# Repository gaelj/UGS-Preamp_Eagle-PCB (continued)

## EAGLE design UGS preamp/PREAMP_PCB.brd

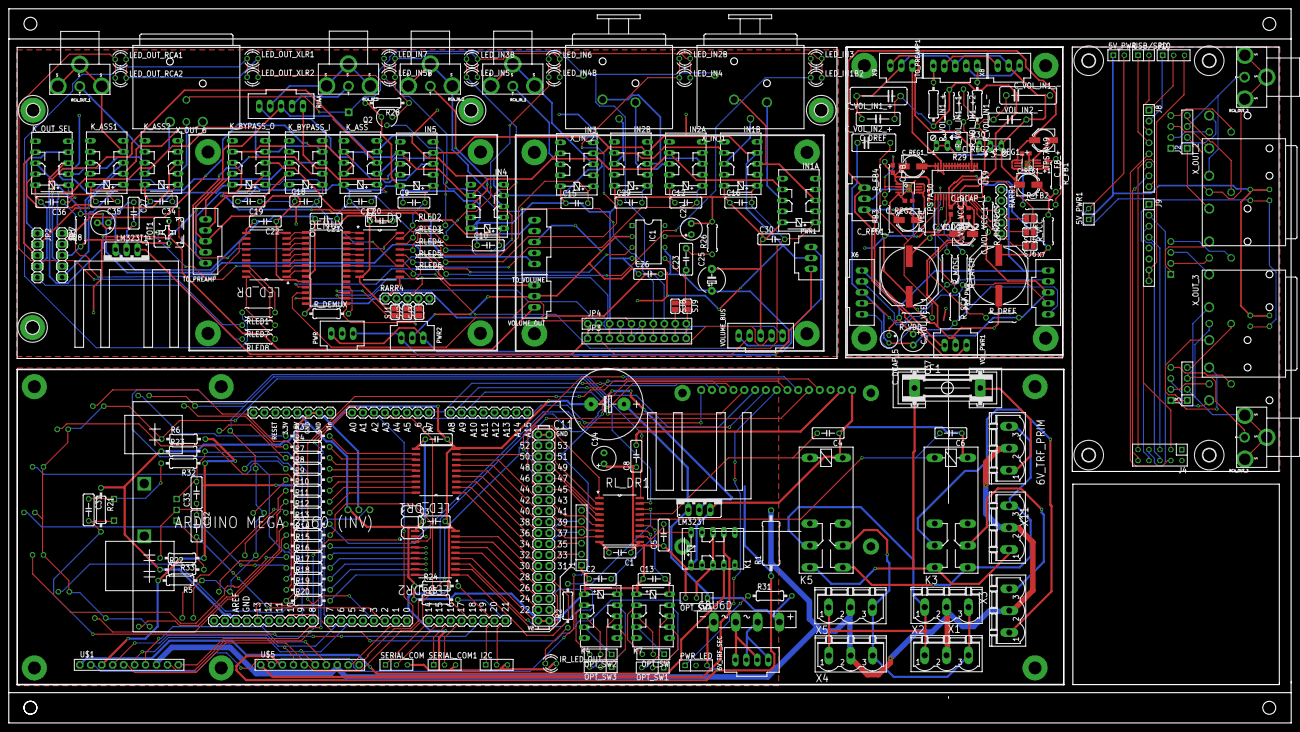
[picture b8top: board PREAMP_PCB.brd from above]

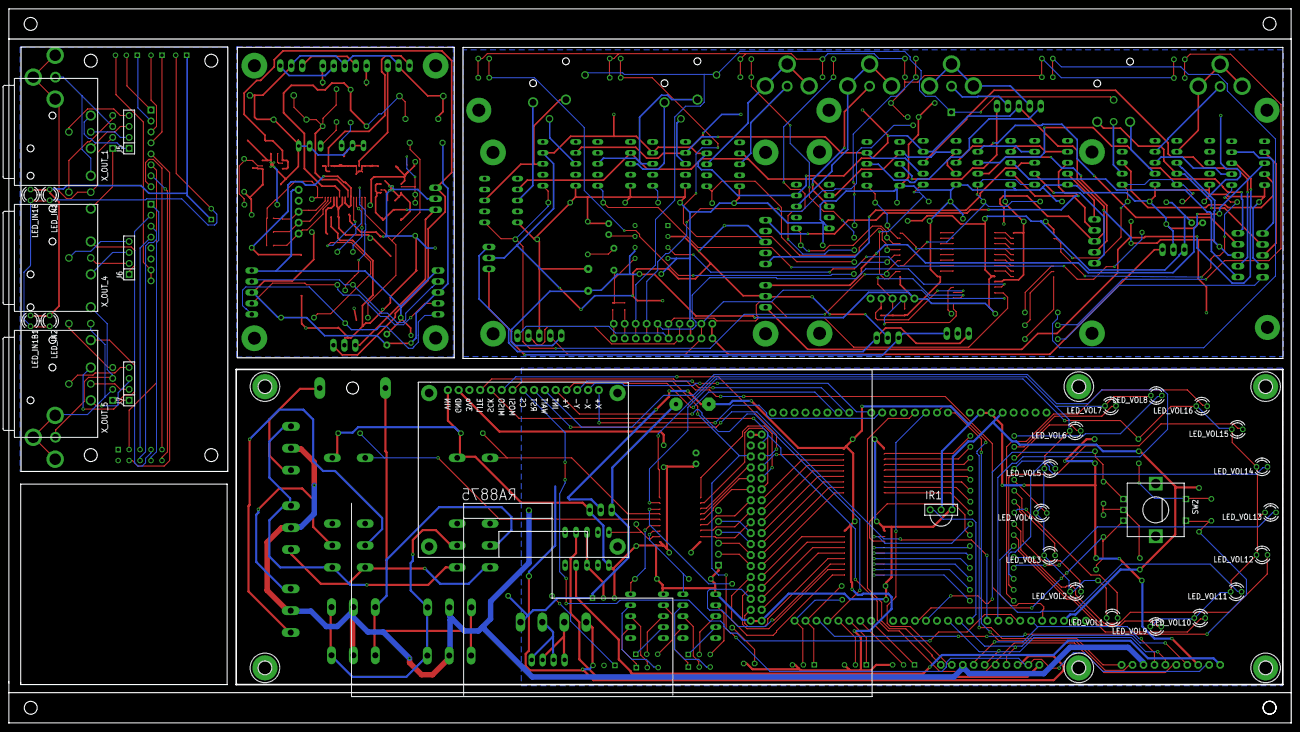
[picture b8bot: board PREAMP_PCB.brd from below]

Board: 2 copper layers, 297.4 x 165.6 mm, 284 parts (34 on the bottom side), 299 nets.

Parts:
5V_PWR, 5V_PWR1: 5V PWR; M1X2
6V_TRF_PRIM: 5V_TRF_PRIM; MSTBV3
6V_TRF_SEC: 6V_TRF_SEC; 70543-04
C1, C2, C3, C4, C5, C6, C7, C8, C9, C10, C12, C13, C15, C16, C17, C18, C19, C20, C21, C22, C26, C27, C29, C30, C31, C32, C33, C34, C35, C36: 100n; C050-025X075
C11: 4700µ; E7,5-16
C14, C28, C37: 470µ; E2,5-6
C23: 47nF; C5B3
C24: 1µF; E2,5-5
C25: 100µF; E5-6
C_DCAP_1: 100n; C0603
C_DCAP_2: 10µ24V; PANASONIC_C
C_DCAP_5: 1µ 5V; E1,8-4
C_DREF: 470n; C075-042X103
C_FB_+: 10n; C0603
C_FB_-: 10n; C0603
C_REG1_+, C_REG1_+1, C_REG1_-, C_REG1_-1: 10µ24V; PANASONIC_C
C_REG2_+, C_REG2_-: 10n; C0603
C_VOL_IN1_+, C_VOL_IN1_-: 1n; C102-043X133
C_VOL_IN2_+, C_VOL_IN2_-: 100p; C075-032X103
C_VOL_VCC_1: 470µ 24V; PANASONIC_H13
C_VOL_VCC_2: 100n; C0603
C_VOL_VEE_1: 470µ 24V; PANASONIC_H13
C_VOL_VEE_2: 100n; C0603
DEMUX: 23S17; SO28W
F1: 300mA; GSH15
GBU6D: 6A; GBU4S
H1, H3, H6, H7, H8, H9, H11, H12, H13, H15: MOUNT-PAD-ROUND3.0; 3,0-PAD
H2, H4, H5, H10: MOUNT-HOLE3.0; 3,0
I2C: CON_HEADER_1X03-PTH; M1X3
IC1: LM386; DIL08
IN1A: IN1A; G6H2-100
IN1B: IN1B; G6H2-100
IN2A: IN2A; G6H2-100
IN2B: IN2B; G6H2-100
IN3: IN3; G6H2-100
IN4: IN4; G6H2-100
IN5: IN5; G6H2-100
IR1: IR; TSOP17_TB1
IR_LED_OUT: IR out; LED3MM
J1: CON_HEADER_1X06-PTH; M1X6
J2, J3: CON_HEADER_1X04; M1X4
J4: DAC; M2X5
J5: CON_OUT_1; M1X4
J6: CON_OUT_2; M1X4
J7: CON_OUT_3; M1X4
J8: ARD1; M1X8
J9: ARD2; M1X8
J10: SERIAL; M1X3
JP1: OUT/IN SELECTED; 1X05
JP2: OUTPUT; 1X05
JP3, JP4: PINHD-1X10; 1X10-BIG
K1, K4, K7: G6H2-100
K3, K5: 4052; F4052
K_ASS: K_ASS_I; G6H2-100
K_ASS1: K_ASS_O_GND; G6H2-100
K_ASS2: K_ASS_O; G6H2-100
K_BYPASS_I: BYPASS_I; G6H2-100
K_BYPASS_O: BYPASS_O; G6H2-100
K_OUT_SEL: K_OUT_SEL; G6H2-100
LED_DR, LED_DR1, LED_DR2: 2803; SOIC127P1030X265-18N
LED_IN1, LED_IN1B, LED_IN1B1, LED_IN1B2, LED_IN2, LED_IN2B, LED_IN3, LED_IN3B, LED_IN4, LED_IN4B, LED_IN5, LED_IN5B, LED_IN6, LED_IN7: LED3MM
LED_OUT_RCA1, LED_OUT_RCA2: LED3MM
LED_OUT_XLR1, LED_OUT_XLR2: LED3MM
LED_VOL1, LED_VOL2, LED_VOL3, LED_VOL4, LED_VOL5, LED_VOL6, LED_VOL7, LED_VOL8, LED_VOL9, LED_VOL10, LED_VOL11, LED_VOL12, LED_VOL13, LED_VOL14, LED_VOL15, LED_VOL16: LED3MM
LM323T, LM323T1: 5V REG; TO220S
OPT_SW, OPT_SW1, OPT_SW2, OPT_SW3, OPT_SW4: CON_HEADER_1X03-PTH; M1X3
PCB2: ARDUINO_MEGA2560_INV
POT1: 500k; B25P
PRE_PWR: TO_PRE_PWR; 70543-03
PWR, PWR1, PWR2: PWR; 70543-03
PWR_LED: CON_HEADER_1X03-PTH; M1X3
Q2: BS170; SOT54E
R1: 10R 1W; 0411/15
R2, R32, R33: 330; 0207/10
R3, R4, R7, R8, R9, R10, R11, R12, R13, R14, R15, R16, R17, R18, R19, R20, R31: 1k; 0207/10
R5, R6, R21, R22, R23, R24, R25: 10k; 0207/10
R26: 10; 0207/7
R27: 500k; 0207/7
R28: 10k PWM; 0207/10
R29, R30: 20k; RJ9W
RARR1, RARR4: 10k; 1X05
RCA_IN_1: IN1; MONO_JACK
RCA_IN_2: IN2; MONO_JACK
RCA_IN_3: IN3_RIAA; MONO_JACK
RCA_OUT_1: OUT1; MONO_JACK
RCA_OUT_2: OUT_L; MONO_JACK
RCA_OUT_3: OUT_R; MONO_JACK
RIAA: TO_RIAA; 70543-05
RLED1, RLED2, RLED3, RLED4, RLED5, RLED6, RLED7, RLED8: 45 LED; 0207/7
RL_DR, RL_DR1: 2803; SOIC127P1030X265-18N
R_DEMUX: 10k; RTH025W
R_DREF: 10k; 0207/7
R_FB1, R_FB4: 1,17M; 0207/7
R_FB2, R_FB3: 100k; 0207/7
R_LATCH: 100; 0207/7
R_MOSI: 100; 0207/7
R_PROTECT: 100; 0207/7
R_SCK: 100; 0207/7
R_VCC: 1; 0207/7
R_VDD: 10k; 0207/7
R_VEE: 1; 0207/7
R_VOL_IN1_+, R_VOL_IN1_-: 470; 0207/10
R_VOL_IN1_+1, R_VOL_IN1_+2: 20k; 0207/7
SERIAL_COM, SERIAL_COM1: CON_HEADER_1X03-PTH; M1X3
SJ1, SJ8, SJ9: A0; SJ
SJ2: A1; SJ
SJ3: A2; SJ
SJ4: ADR0; SJ
SJ5: ADR1; SJ
SJ6: ADR2; SJ
SW2: EC12E_SW; ALPS_EC12E_SW
T1: PAD_TERMINAL-1.02MM_SQUARE; CON_PAD_SQUARE_1.02MM
TO_PREAMP, TO_PREAMP1: TO_PREAMP; 70543-05
TO_VOLUME: TO_VOLUME; 70543-05
TPS7A30: TPS7A30; MSOP8
TPS7A49: TPS7A49; MSOP8
U$1, U$5: RELAY BOARD; 1X10-BIG
U$2, U$7: HEATSINK
U$3: RA8875
U$4: 5"TFT; 5_TFT
U$6, U$8, U$10: UGS
U$9: MUSES72320; SSOP32
USB/SPD: IN_SEL; M1X2
VOLUME_BUS: VOLUME_BUS; 70543-05
VOLUME_OUT: VOLUME_OUT; 70543-03
VOL_PWR1: PWR_IN; 70543-03
X1: 220V PR13; MSTBV3
X2: 220V PR14; MSTBV3
X3: 220V PR2; MSTBV3
X4: 220V PR11; MSTBV3
X5: 220V PR12; MSTBV3
X6, X7: PWR+SPI; 70543-05
X8: INPUT; 70543-03
X9: OUTPUT; 70543-03
X11: 220V AC IN; MSTBV3
X_IN_1: X_IN_1; NC3FAH2
X_IN_2: X_IN_2; NC3FAH2
X_OUT_1: OUT_1; NC3MBH
X_OUT_2: OUT_S_L; NC3MBH
X_OUT_3: OUT_S_R; NC3MBH
X_OUT_4: OUT_2; NC3MBH
X_OUT_5: OUT_3; NC3MBH
X_OUT_6: X_OUT; NC3MBH

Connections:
44.1KHZ: J4.10, J8.7
48KHZ: J4.9, J8.8
88.2KHZ: J4.8, J9.1
96KHZ: J4.7, J9.2
176.4KHZ: J4.6, J9.3
192KHZ: J4.5, J9.4
+5V: C1.1, C2.1, C3.1, C4.1, C5.1, C6.1, C7.1, C8.1, C13.1, C14.+, IR1.VO, J1.1, K1.1, K3.1, K4.1, K5.1, K7.1, LED_DR1.10, LED_DR2.10, LM323T.3, OPT_SW4.3, PCB2.5V, PCB2.5V., PCB2.5V.., PCB2.AREF, R21.1, R22.1, R23.1, R24.1, R25.1, RL_DR1.10, U$3.VIN
+5V1: 5V_PWR.1, 5V_PWR1.1, LED_IN1.A, LED_IN1B.A, LED_IN1B1.A, LED_IN2.A
+5V2: C20.2, C21.2, C22.2, C25.+, C26.2, C27.1, C28.+, DEMUX.9, IC1.6, LED_DR.10, LM323T1.3, RARR4.1, RL_DR.10, R_DEMUX.1, VOLUME_BUS.1
+5V3: C37.+, C_DCAP_5.+, RARR1.1, R_VDD.2, X6.1, X7.1
+5V_RAW: JP3.1, JP4.1, LM323T1.1
AUDIOSTREAM: J4.3, J8.6
A_VCC: C_FB_+.2, C_REG1_+1.+, R_FB1.2, R_VCC.2, TPS7A49.1
A_VEE: C_FB_-.2, C_REG1_-1.-, R_FB4.2, R_VEE.2, TPS7A30.1
BYPASS+: K_BYPASS_I.S1, K_BYPASS_O.S1
BYPASS-: K_BYPASS_I.S2, K_BYPASS_O.S2
EARTH: 6V_TRF_PRIM.2, R1.2, U$1.8, U$5.8, X1.2, X2.2, X3.2, X4.2, X5.2, X11.2
EARTH1: JP3.8, JP4.8, T1.P, X_IN_1.G, X_IN_2.G, X_OUT_6.G
GND: C1.2, C3.2, C7.2, C8.2, C11.-, C14.-, GBU6D.-, I2C.3, IR1.VS, IR_LED_OUT.K, J1.6, LED_DR1.9, LED_DR2.9, LM323T.2, PCB2.GND., PCB2.GND.., PCB2.GND..., PCB2.GND...., PWR_LED.3, R1.1, R5.2, R6.2, R32.1, R33.1, RL_DR1.9, SERIAL_COM.3, SERIAL_COM1.3, U$1.3, U$3.GND, U$5.3
GND1: C9.1, C10.1, C12.1, C15.1, C16.1, C17.2, C18.1, C19.2, C20.1, C21.1, C22.1, C24.-, C25.-, C26.1, C27.2, C28.-, C29.1, C30.1, C34.2, C35.2, C36.2, DEMUX.10, IC1.4, IN1A.10, IN1B.10, IN2A.10, IN2B.10, IN3.10, IN4.10, IN5.10, JP2.4, JP3.3, JP4.3, K_ASS.10, K_ASS1.10, K_ASS2.10, K_BYPASS_I.10, K_BYPASS_O.10, K_OUT_SEL.10, LED_DR.9, LM323T1.2, Q2.S, R26.2, R28.2, RL_DR.9, SJ1.1, SJ2.1, SJ3.1, VOLUME_BUS.3
GND2: C37.-, C_DCAP_5.-, C_DREF.1, R_DREF.2, R_PROTECT.2, X6.3, X7.3
GND_5V: J9.7, J9.8, J10.3
GND_AUDIO: IC1.2, IN1B.S1, IN2B.S1, IN3.S1, IN4.S1, JP1.3, K_ASS.S1, K_ASS1.P1, POT1.1, PWR.2, PWR1.2, PWR2.2, R27.1, RIAA.3, TO_PREAMP.3, TO_VOLUME.3, VOLUME_OUT.2
GND_AUDIO1: C_REG1_+.-, C_REG1_+1.-, C_REG1_-.+, C_REG1_-1.+, C_REG2_+.2, C_REG2_-.2, C_VOL_IN1_+.2, C_VOL_IN1_-.2, C_VOL_IN2_+.2, C_VOL_IN2_-.2, C_VOL_VCC_1.-, C_VOL_VCC_2.2, C_VOL_VEE_1.+, C_VOL_VEE_2.1, PRE_PWR.2, R29.A, R29.S, R30.A, R30.S, R_FB2.1, R_FB3.1, TO_PREAMP1.3, TPS7A30.4, TPS7A30.H, TPS7A49.4, TPS7A49.H, U$9.1, U$9.2, U$9.4, U$9.5, U$9.6, U$9.7, U$9.8, U$9.9, U$9.10, U$9.11, U$9.12, U$9.13, U$9.15, U$9.16, VOL_PWR1.2, X8.2, X9.2
GND_IN_RIAA: RCA_IN_3.SLEEVE, RCA_IN_3.SLEEVE1, RCA_IN_3.SLEEVE2, RIAA.4
GND_OUT_ASSYM: K_ASS1.S1, RCA_OUT_1.SLEEVE, RCA_OUT_1.SLEEVE1, RCA_OUT_1.SLEEVE2
GND_OUT_SYM: JP2.2, K_ASS1.O1, X_OUT_6.1
HOST_ACTIVE: J4.4, J8.5
IN_SYM+: IN1A.S2, IN2A.S2, IN3.S2, IN4.S2, IN5.S2, K_ASS.O2, K_ASS.S2
IN_SYM-: IN1B.S2, IN2B.S2, IN5.S1, K_ASS.O1
IN_VOL+: K_BYPASS_O.P1, TO_VOLUME.1
IN_VOL-: K_BYPASS_O.P2, TO_VOLUME.5
IO22: LED_DR2.5, PCB2.22
IO23: LED_DR2.4, PCB2.23
IO24: LED_DR2.6, PCB2.24
IO25: LED_DR2.3, PCB2.25
IO26: LED_DR2.7, PCB2.26
IO27: LED_DR2.2, PCB2.27
IO28: LED_DR2.8, PCB2.28
IO29: LED_DR2.1, PCB2.29
IO30: LED_DR1.1, PCB2.30
IO31: J1.2, PCB2.31
IO32: LED_DR1.2, PCB2.32
IO33: J1.3, PCB2.33
IO34: LED_DR1.3, PCB2.34
IO35: J1.4, PCB2.35
IO36: LED_DR1.4, PCB2.36
IO37: J1.5, PCB2.37
IO38: LED_DR1.5, PCB2.38
IO39: PCB2.39, RL_DR1.8
IO40: LED_DR1.6, PCB2.40
IO41: PCB2.41, RL_DR1.7
IO42: LED_DR1.7, PCB2.42
IO43: PCB2.43, RL_DR1.6
IO44: PCB2.44, RL_DR1.2
IO45: PCB2.45, RL_DR1.5
IO46: PCB2.46, RL_DR1.1
IO47: PCB2.47, RL_DR1.4
IO48: LED_DR1.8, PCB2.48
IO49: PCB2.49, RL_DR1.3
IR_IN: IR1.GND, PCB2.7
JHGCD: R_PROTECT.1, SJ4.1, SJ5.1, SJ6.1, U$9.32
L+: J2.3, RCA_OUT_2.TIP, X_OUT_2.2
L+1: J5.3, X_OUT_1.2
L+2: J6.3, X_OUT_4.2
L+3: J7.3, X_OUT_5.2
L-: J2.2, RCA_OUT_2.SLEEVE, RCA_OUT_2.SLEEVE1, RCA_OUT_2.SLEEVE2, X_OUT_2.3
L-1: J5.2, X_OUT_1.3
L-2: J6.2, X_OUT_4.3
L-3: J7.2, X_OUT_5.3
LED1: LED_IN1B2.A, LED_IN3.A, RLED6.2
LED2: LED_IN2B.A, LED_IN4.A, RLED5.2
LED3: LED_IN3B.A, LED_IN5.A, RLED4.2
LED4: LED_IN4B.A, LED_IN6.A, RLED3.2
LED5: LED_IN5B.A, LED_IN7.A, RLED2.2
LED6: LED_OUT_XLR1.A, LED_OUT_XLR2.A, RLED1.2
LED7: LED_OUT_RCA1.A, LED_OUT_RCA2.A, RLED7.2
LED8: JP2.5, RLED8.2
LED_GND: 5V_PWR.2, 5V_PWR1.2, LED_IN1.K, LED_IN1B.K, LED_IN1B1.K, LED_IN2.K
LED_PWM_GND: LED_IN1B2.K, LED_IN2B.K, LED_IN3.K, LED_IN3B.K, LED_IN4.K, LED_IN4B.K, LED_IN5.K, LED_IN5B.K, LED_IN6.K, LED_IN7.K, LED_OUT_RCA1.K, LED_OUT_RCA2.K, LED_OUT_XLR1.K, LED_OUT_XLR2.K, Q2.D, R28.1
L_GND: J2.1, X_OUT_2.1
L_GND1: J5.1, X_OUT_1.1
L_GND2: J6.1, X_OUT_4.1
L_GND3: J7.1, X_OUT_5.1
MAINS_L: F1.1, K3.S1, K5.S1, X11.1
MAINS_N: 6V_TRF_PRIM.3, K3.S2, K5.S2, X11.3
MISO: PCB2.50, U$3.MISO
MOSI: PCB2.51, U$1.2, U$3.MOSI, U$5.2
MOSI1: DEMUX.13, JP3.2, JP4.2, VOLUME_BUS.2
MOSI2: R_MOSI.2, X6.2, X7.2
MUX_CS: PCB2.5, U$1.6, U$5.6
MUX_CS1: DEMUX.11, JP3.6, JP4.6
unnamed: K4.P1, OPT_SW2.2
unnamed: R2.2, RL_DR1.16
unnamed: IR_LED_OUT.A, R2.1
unnamed: LED_VOL1.A, R12.1
unnamed: PCB2.14, SERIAL_COM.1
unnamed: PCB2.15, SERIAL_COM.2
unnamed: LED_VOL1.K, LED_VOL2.K, LED_VOL3.K, LED_VOL4.K, LED_VOL5.K, LED_VOL6.K, LED_VOL7.K, LED_VOL8.K, R5.1, RL_DR1.18
unnamed: K4.S1, OPT_SW2.1
unnamed: K4.O1, OPT_SW2.3
unnamed: LED_VOL2.A, R11.1
unnamed: K7.P2, OPT_SW1.2
unnamed: LED_VOL3.A, R10.1
unnamed: LED_VOL4.A, R9.1
unnamed: LED_VOL5.A, R8.1
unnamed: LED_VOL6.A, R7.1
unnamed: LED_VOL7.A, R4.1
unnamed: LED_VOL8.A, R3.1
unnamed: LED_DR2.11, R13.2
unnamed: LED_DR2.12, R14.2
unnamed: LED_VOL9.K, LED_VOL10.K, LED_VOL11.K, LED_VOL12.K, LED_VOL13.K, LED_VOL14.K, LED_VOL15.K, LED_VOL16.K, R6.1, RL_DR1.17
unnamed: LED_DR2.13, R15.2
unnamed: LED_DR2.14, R16.2
unnamed: LED_DR2.15, R17.2
unnamed: LED_DR2.16, R18.2
unnamed: LED_DR2.17, R19.2
unnamed: LED_DR2.18, R20.2
unnamed: K7.S2, OPT_SW1.1
unnamed: LED_DR1.11, R3.2
unnamed: LED_DR1.12, R4.2
unnamed: K4.P2, OPT_SW3.2
unnamed: LED_DR1.13, R7.2
unnamed: K7.P1, OPT_SW.2
unnamed: LED_DR1.14, R8.2
unnamed: LED_DR1.15, R9.2
unnamed: LED_DR1.16, R10.2
unnamed: LED_DR1.17, R11.2
unnamed: LED_DR1.18, R12.2
unnamed: 6V_TRF_SEC.2, 6V_TRF_SEC.4, GBU6D.AC1
unnamed: 6V_TRF_SEC.1, 6V_TRF_SEC.3, GBU6D.AC2
unnamed: K7.O2, OPT_SW1.3
unnamed: LED_VOL9.A, R13.1
unnamed: LED_VOL10.A, R14.1
unnamed: LED_VOL11.A, R15.1
unnamed: IN3.P1, RCA_IN_1.SLEEVE, RCA_IN_1.SLEEVE1, RCA_IN_1.SLEEVE2
unnamed: IN1A.P2, X_IN_1.2
unnamed: IN1B.P2, X_IN_1.3
unnamed: DEMUX.8, LED_DR.1
unnamed: DEMUX.7, LED_DR.2
unnamed: DEMUX.6, LED_DR.3
unnamed: DEMUX.5, LED_DR.4
unnamed: DEMUX.4, LED_DR.5
unnamed: DEMUX.3, LED_DR.6
unnamed: LED_VOL12.A, R16.1
unnamed: LED_VOL13.A, R17.1
unnamed: LED_VOL14.A, R18.1
unnamed: K3.P2, X3.3
unnamed: LED_VOL15.A, R19.1
unnamed: LED_VOL16.A, R20.1
unnamed: K7.S1, OPT_SW.1
unnamed: PCB2.16, SERIAL_COM1.1
unnamed: PCB2.17, SERIAL_COM1.2
unnamed: DEMUX.2, LED_DR.7
unnamed: DEMUX.1, LED_DR.8
unnamed: K4.S2, OPT_SW3.1
unnamed: K3.P1, X3.1
unnamed: DEMUX.17, RARR4.4, SJ3.2
unnamed: IN4.P1, RCA_IN_2.SLEEVE, RCA_IN_2.SLEEVE1, RCA_IN_2.SLEEVE2
unnamed: IN2A.P2, X_IN_2.2
unnamed: IN2B.P2, X_IN_2.3
unnamed: DEMUX.16, RARR4.3, SJ2.2
unnamed: DEMUX.15, RARR4.2, SJ1.2
unnamed: IN3.P2, RCA_IN_1.TIP
unnamed: 6V_TRF_PRIM.1, F1.2
unnamed: K7.O1, OPT_SW.3
unnamed: PCB2.A0, U$1.9
unnamed: IN4.P2, RCA_IN_2.TIP
unnamed: DEMUX.18, R_DEMUX.2
unnamed: C23.2, R26.1
unnamed: IC1.3, POT1.2
unnamed: C24.+, IC1.7
unnamed: IN2A.P1, IN2B.P1, X_IN_2.1
unnamed: IN1A.P1, IN1B.P1, X_IN_1.1
unnamed: DEMUX.21, RL_DR.8
unnamed: PCB2.A1, U$1.10
unnamed: PCB2.A2, U$5.9
unnamed: PCB2.A3, U$5.10
unnamed: DEMUX.22, RL_DR.7
unnamed: DEMUX.23, RL_DR.6
unnamed: DEMUX.24, RL_DR.5
unnamed: DEMUX.25, RL_DR.4
unnamed: DEMUX.26, RL_DR.3
unnamed: DEMUX.27, RL_DR.2
unnamed: DEMUX.28, RL_DR.1
unnamed: K_ASS2.O2, X_OUT_6.2
unnamed: K_ASS2.O1, X_OUT_6.3
unnamed: K_ASS2.S2, RCA_OUT_1.TIP
unnamed: LED_DR.17, RLED7.1
unnamed: JP3.9, JP4.9, SJ8.2
unnamed: JP3.10, JP4.10, SJ9.2
unnamed: LED_DR.16, RLED1.1
unnamed: LED_DR.18, RLED8.1
unnamed: C29.2, IN2B.1
unnamed: PWR.1, PWR1.1, PWR2.1
unnamed: PWR.3, PWR1.3, PWR2.3
unnamed: C_VOL_VCC_1.+, C_VOL_VCC_2.1, R_VCC.1, U$9.22, U$9.24
unnamed: C_DCAP_1.1, C_DCAP_2.-, C_VOL_VEE_1.-, C_VOL_VEE_2.2, R_VEE.1, U$9.25, U$9.27
unnamed: C_DCAP_1.2, C_DCAP_2.+, U$9.28
unnamed: R_LATCH.1, U$9.20
unnamed: C32.1, C33.1, R33.2, SW2.C
unnamed: R_SCK.1, U$9.19
unnamed: C31.1, R32.2, SW2.D
unnamed: R_MOSI.1, U$9.18
unnamed: RARR1.4, SJ5.2, U$9.30
unnamed: C_DREF.2, R_VDD.1, U$9.17
unnamed: R_DREF.1, U$9.21
unnamed: C_REG2_-.1, TPS7A30.6
unnamed: C_REG2_+.1, TPS7A49.6
unnamed: C_VOL_IN1_+.1, C_VOL_IN2_+.1, R_VOL_IN1_+.2, R_VOL_IN1_+1.1, U$9.26
unnamed: C_VOL_IN1_-.1, C_VOL_IN2_-.1, R_VOL_IN1_+2.1, R_VOL_IN1_-.2, U$9.23
unnamed: R29.E, R_VOL_IN1_+1.2
unnamed: R30.E, R_VOL_IN1_+2.2
unnamed: C_FB_-.1, R_FB3.2, R_FB4.1, TPS7A30.2
unnamed: K4.O2, OPT_SW3.3
unnamed: C_FB_+.1, R_FB1.1, R_FB2.2, TPS7A49.2
unnamed: C_REG1_-.-, PRE_PWR.3, TPS7A30.5, TPS7A30.8, VOL_PWR1.3
unnamed: C_REG1_+.+, PRE_PWR.1, TPS7A49.5, TPS7A49.8, VOL_PWR1.1
unnamed: RARR1.3, SJ4.2, U$9.31
unnamed: RARR1.5, SJ6.2, U$9.29
unnamed: PWR_LED.1, R31.1
unnamed: K5.P1, X1.1, X2.1, X4.1, X5.1
unnamed: K5.P2, X1.3, X2.3, X4.3, X5.3
OUT_EXT+: JP2.1, K_OUT_SEL.S1
OUT_EXT-: JP2.3, K_OUT_SEL.S2
OUT_INT+: K_ASS2.P2, K_OUT_SEL.O1
OUT_INT-: K_ASS2.P1, K_OUT_SEL.O2
OUT_VOL+: K_OUT_SEL.P1, POT1.3, VOLUME_OUT.1
OUT_VOL+1: U$9.3, X9.1
OUT_VOL-: K_OUT_SEL.P2, R27.2, VOLUME_OUT.3
OUT_VOL-1: U$9.14, X9.3
O_SPDIF: J8.3, USB/SPD.2
O_USB: J8.4, USB/SPD.1
PREAMP1_IN+: K_BYPASS_I.O1, TO_PREAMP.2
PREAMP1_IN-: K_BYPASS_I.O2, TO_PREAMP.4
PREAMP1_OUT+: K_BYPASS_O.O1, TO_PREAMP.1
PREAMP1_OUT-: K_BYPASS_O.O2, TO_PREAMP.5
PREAMP_IN+: TO_PREAMP1.2, X8.1
PREAMP_IN-: TO_PREAMP1.4, X8.3
PREAMP_OUT+: R_VOL_IN1_+.1, TO_PREAMP1.1
PREAMP_OUT-: R_VOL_IN1_-.1, TO_PREAMP1.5
PWM: JP3.7, JP4.7, Q2.G
PWM_EXT: PCB2.12, U$1.7, U$5.7
PWM_TFT: PCB2.13, U$3.LITE
R+: J3.3, RCA_OUT_3.TIP, X_OUT_3.2
R-: J3.2, RCA_OUT_3.SLEEVE, RCA_OUT_3.SLEEVE1, RCA_OUT_3.SLEEVE2, X_OUT_3.3
RIAA_IN+: RCA_IN_3.TIP, RIAA.2
RIAA_OUT+: IN5.P2, RIAA.1
RIAA_OUT-: IN5.P1, RIAA.5
RL1: C4.2, K5.2, RL_DR1.15
RL2: C6.2, K3.2, RL_DR1.14
RL3: C13.2, K7.10, RL_DR1.13
RL4: C2.2, K4.10, RL_DR1.12
RL5: C5.2, K1.10, RL_DR1.11
RO_ASYM: C34.1, C35.1, K_ASS1.1, K_ASS2.1, RL_DR.18
RO_OUT: C36.1, K_OUT_SEL.1, LED_DR.11
RS_ASYM: C17.1, K_ASS.1, RL_DR.11
RS_BYPASS: C18.2, C19.1, K_BYPASS_I.1, K_BYPASS_O.1, RL_DR.12
RS_IN1: C16.2, C30.2, IN1A.1, IN1B.1, RLED6.1, RL_DR.13
RS_IN2: C12.2, IN2A.1, RLED5.1, RL_DR.14
RS_IN3: C15.2, IN3.1, RLED4.1, RL_DR.15
RS_IN4: C10.2, IN4.1, RLED3.1, RL_DR.16
RS_IN5: C9.2, IN5.1, RLED2.1, RL_DR.17
RX: J8.1, J10.2
R_GND: J3.1, X_OUT_3.1
SCK: PCB2.52, U$1.5, U$3.SCK, U$5.5
SCK1: DEMUX.12, JP3.5, JP4.5, VOLUME_BUS.5
SCK2: R_SCK.2, X6.5, X7.5
SCL: I2C.2, PCB2.21, R25.2
SDA: I2C.1, PCB2.20, R24.2
SELECTED+: JP1.2, K_ASS.P2
SELECTED-: JP1.4, K_ASS.P1
SHIELD_L: J2.4, X_OUT_2.G
SHIELD_L1: J5.4, X_OUT_1.G
SHIELD_L2: J6.4, X_OUT_4.G
SHIELD_L3: J7.4, X_OUT_5.G
SHIELD_R: J3.4, X_OUT_3.G
SW_ENC1: C32.2, PCB2.2, R22.2, SW2.B
SW_ENC2: C33.2, PCB2.3, R23.2, SW2.A
SW_PUSH: C31.2, PCB2.19, R21.2, SW2.E
TFT_CS: PCB2.11, U$3.CS
TFT_INT: PCB2.18, U$3.INT
TFT_RST: PCB2.8, U$3.RST
TFT_WAIT: PCB2.9, U$3.WAIT
TFT_X+: PCB2.A6, U$3.X+
TFT_X-: PCB2.A7, U$3.X-
TFT_Y+: PCB2.A9, U$3.Y+
TFT_Y-: PCB2.A8, U$3.Y-
TO_PREAMP+: JP1.1, K_BYPASS_I.P1
TO_PREAMP-: JP1.5, K_BYPASS_I.P2
TX: J8.2, J10.1
VOL_CS: PCB2.6, U$1.4, U$5.4
VOL_CS1: JP3.4, JP4.4, VOLUME_BUS.4
VOL_CS2: R_LATCH.2, X6.4, X7.4
VU_METER: C23.1, IC1.5, SJ8.1, SJ9.1
V_RECT: C11.+, GBU6D.+, LM323T.1, OPT_SW4.1, R31.2
V_RECT1: K1.S1, U$1.1
V_RECT2: K1.S2, U$5.1
V_RECT_SEL: K1.P1, K1.P2, OPT_SW4.2

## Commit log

2016-04-20 :octocat: Added .gitattributes & .gitignore files
2016-04-21 UGS Preamp electrical diagram & PCB layout
